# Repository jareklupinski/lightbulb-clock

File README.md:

# lightbulb-clock
Using 1970's Nixie Tube Technology for Timekeeping

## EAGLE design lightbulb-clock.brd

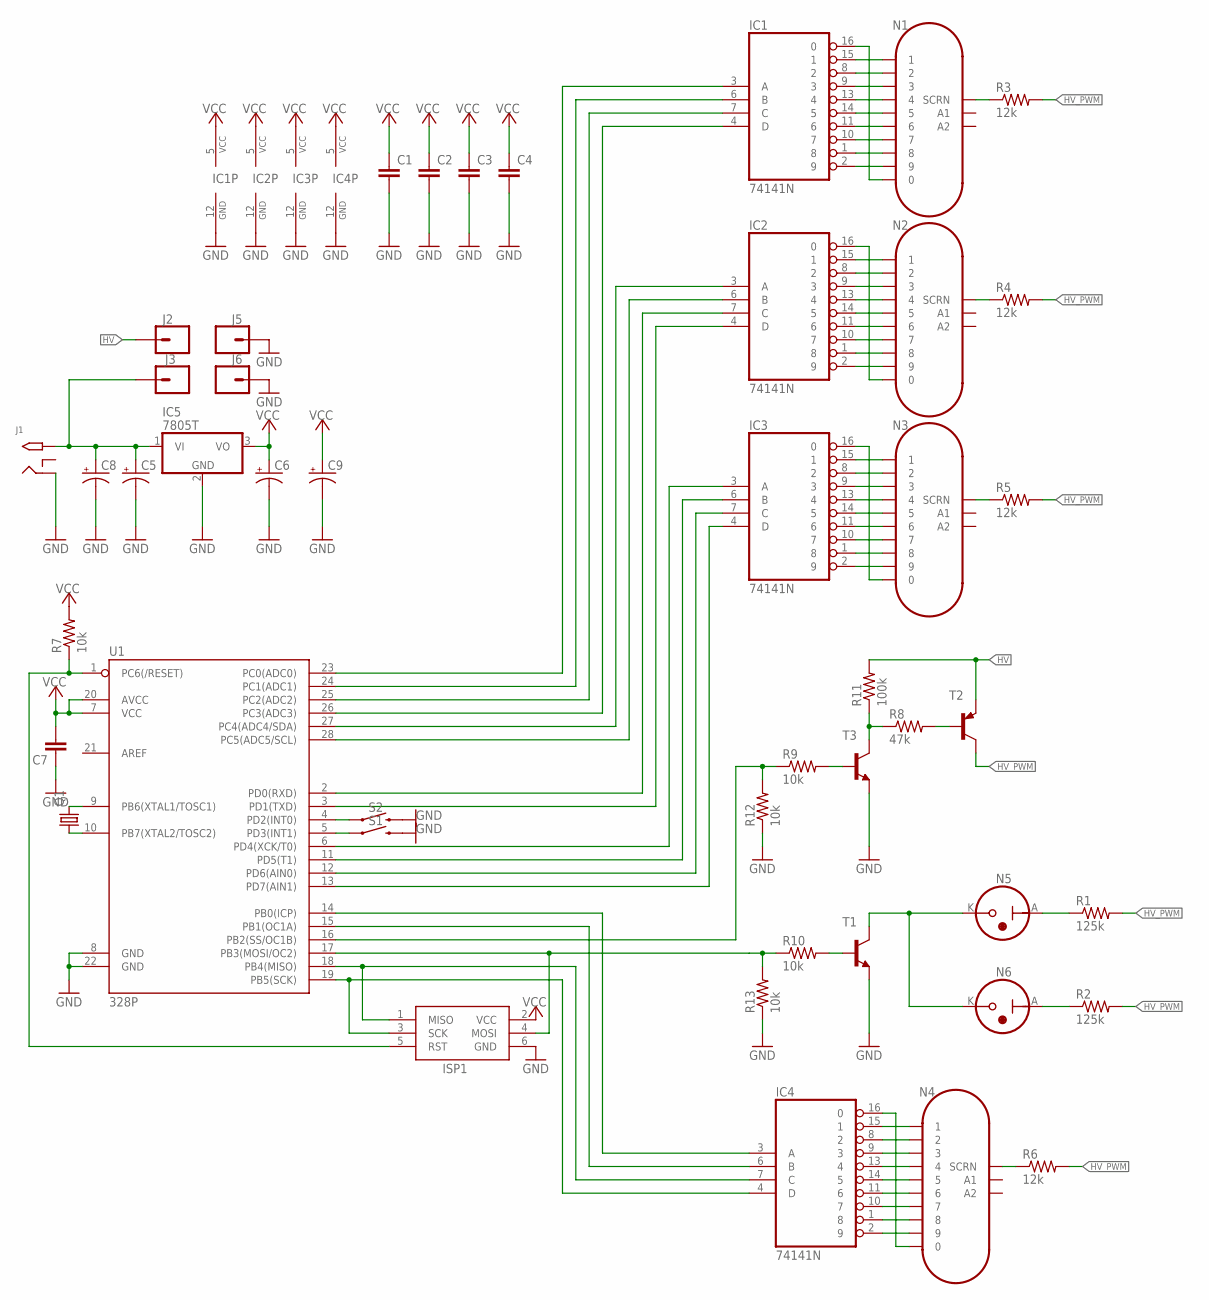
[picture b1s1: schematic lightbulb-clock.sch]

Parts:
C1, C2, C3, C4, C7: C-EU025-024X044; C025-024X044
C5, C6, C8, C9: CPOL-USE3.5-8; E3,5-8
IC1, IC2, IC3, IC4: 74141N; DIL16
IC5: 7805T; TO220H
ISP1: AVRISP-6; AVRISP
J1: 2.1MMJACKTHM; PJ-102A
J2, J3, J5, J6: CONN_01; 1X01
N1, N2, N3, N4: IN-4
N5, N6: INS-1
Q1: CRYSTALTC26H; TC26H
R1, R2: 125k; 0204/5
R3, R4, R5, R6: 12k; 0204/5
R7, R9, R10, R12, R13: 10k; 0204/5
R8: 47k; 0204/5
R11: 100k; 0204/5
S1, S2: MOMENTARY-SWITCH-SPST-PTH-6.0MM; TACTILE_SWITCH_PTH_6.0MM
T1, T3: MPSA42-NPN-TO92-EBC; TO92-EBC
T2: MPSA92-PNP-TO92-EBC; TO92-EBC
U1: 328P; DIP28

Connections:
GND: C1.2, C2.2, C3.2, C4.2, C5.-, C6.-, C7.1, C8.-, C9.-, IC1.12 (GND), IC2.12 (GND), IC3.12 (GND), IC4.12 (GND), IC5.2 (GND), ISP1.6 (GND), J1.RING, J5.1, J6.1, R12.1, R13.1, S1.3 (2), S2.3 (2), T1.E, T3.E, U1.8 (GND), U1.22 (GND)
HV: J2.1, R11.2, T2.E
HV_PWM: R1.2, R2.2, R3.2, R4.2, R5.2, R6.2, T2.C
unnamed: IC1.1 (8), N1.8
unnamed: IC1.2 (9), N1.9
unnamed: IC1.8 (2), N1.2
unnamed: IC1.9 (3), N1.3
unnamed: IC1.10 (7), N1.7
unnamed: IC1.11 (6), N1.6
unnamed: IC1.13 (4), N1.4
unnamed: IC1.14 (5), N1.5
unnamed: IC1.15 (1), N1.1
unnamed: IC1.16 (0), N1.0
unnamed: IC2.1 (8), N2.8
unnamed: IC2.2 (9), N2.9
unnamed: IC2.8 (2), N2.2
unnamed: IC2.9 (3), N2.3
unnamed: IC2.10 (7), N2.7
unnamed: IC2.11 (6), N2.6
unnamed: IC2.13 (4), N2.4
unnamed: IC2.14 (5), N2.5
unnamed: IC2.15 (1), N2.1
unnamed: IC2.16 (0), N2.0
unnamed: IC3.1 (8), N3.8
unnamed: IC3.2 (9), N3.9
unnamed: IC3.8 (2), N3.2
unnamed: N1.S (SCRN), R3.1
unnamed: IC3.9 (3), N3.3
unnamed: N2.S (SCRN), R4.1
unnamed: N3.S (SCRN), R5.1
unnamed: N4.S (SCRN), R6.1
unnamed: N5.A, R1.1
unnamed: N6.A, R2.1
unnamed: IC3.10 (7), N3.7
unnamed: IC3.11 (6), N3.6
unnamed: IC3.13 (4), N3.4
unnamed: IC3.14 (5), N3.5
unnamed: IC3.15 (1), N3.1
unnamed: IC3.16 (0), N3.0
unnamed: IC4.1 (8), N4.8
unnamed: IC4.2 (9), N4.9
unnamed: IC4.8 (2), N4.2
unnamed: IC4.9 (3), N4.3
unnamed: IC4.10 (7), N4.7
unnamed: IC4.11 (6), N4.6
unnamed: IC4.13 (4), N4.4
unnamed: IC4.14 (5), N4.5
unnamed: IC4.15 (1), N4.1
unnamed: IC4.16 (0), N4.0
unnamed: N5.K, N6.K, T1.C
unnamed: ISP1.4 (MOSI), R10.1, R13.2, U1.17 (PB3(MOSI/OC2))
unnamed: C5.+, C8.+, IC5.1 (VI), J1.TIP, J3.1
unnamed: ISP1.5 (RST), R7.1, U1.1 (PC6(/RESET))
unnamed: IC4.7 (C), ISP1.1 (MISO), U1.18 (PB4(MISO))
unnamed: IC4.4 (D), ISP1.3 (SCK), U1.19 (PB5(SCK))
unnamed: R8.2, T2.B
unnamed: IC3.4 (D), U1.13 (PD7(AIN1))
unnamed: IC4.6 (B), U1.15 (PB1(OC1A))
unnamed: R8.1, R11.1, T3.C
unnamed: R9.2, T3.B
unnamed: R9.1, R12.2, U1.16 (PB2(SS/OC1B))
unnamed: R10.2, T1.B
unnamed: IC4.3 (A), U1.14 (PB0(ICP))
unnamed: IC3.7 (C), U1.12 (PD6(AIN0))
unnamed: IC3.6 (B), U1.11 (PD5(T1))
unnamed: IC3.3 (A), U1.6 (PD4(XCK/T0))
unnamed: IC2.4 (D), U1.3 (PD1(TXD))
unnamed: IC2.7 (C), U1.2 (PD0(RXD))
unnamed: IC2.6 (B), U1.28 (PC5(ADC5/SCL))
unnamed: S2.1, U1.4 (PD2(INT0))
unnamed: Q1.2, U1.9 (PB6(XTAL1/TOSC1))
unnamed: Q1.1, U1.10 (PB7(XTAL2/TOSC2))
unnamed: S1.1, U1.5 (PD3(INT1))
unnamed: IC2.3 (A), U1.27 (PC4(ADC4/SDA))
unnamed: IC1.4 (D), U1.26 (PC3(ADC3))
unnamed: IC1.7 (C), U1.25 (PC2(ADC2))
unnamed: IC1.6 (B), U1.24 (PC1(ADC1))
unnamed: IC1.3 (A), U1.23 (PC0(ADC0))
VCC: C1.1, C2.1, C3.1, C4.1, C6.+, C7.2, C9.+, IC1.5 (VCC), IC2.5 (VCC), IC3.5 (VCC), IC4.5 (VCC), IC5.3 (VO), ISP1.2 (VCC), R7.2, U1.7 (VCC), U1.20 (AVCC)

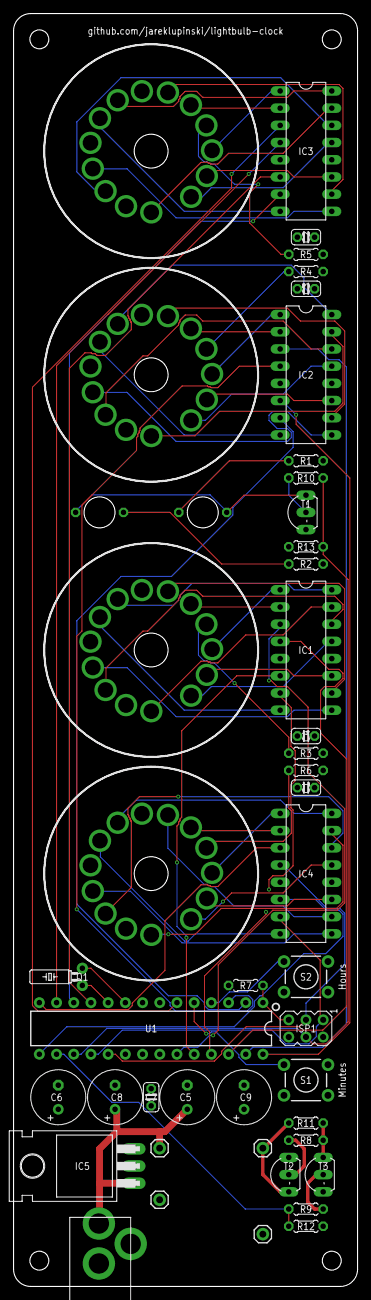
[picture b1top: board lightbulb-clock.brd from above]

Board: 4 copper layers, 50.8 x 188.0 mm, 46 parts (0 on the bottom side), 79 nets.

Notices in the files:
parts and their libraries:
SparkFun-IC-Microcontroller: Licensing: Creative Commons ShareAlike 4.0 International - https://creativecommons.org/licenses/by-sa/4.0
